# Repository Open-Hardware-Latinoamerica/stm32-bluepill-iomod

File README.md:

# STM32-BluePill Digital I/O Board

This Open Source Hardware PCB proyect is a tool for teach µController (microcontroller) programming. Feel free to use, modifie or improobe it in any way you want. The schematics and the layout was designed on [KiCad EDA Software](https://kicad.org/).

More information (Spanish only): [BluePill STM32 Digital I/O Board v3.0](https://blog.tute-avalos.com/2021/08/18/blue-pill-stm32-digital-i-o-board-v3-0/)

- - -

Este PCB es un poryecto de Hardware Libre y Abierto, pensado para enseñar programación de µControladores (microcontroladores). Sientase libre de usarlo, modificarlo y/o mejorarlo en cualquier sentido que desee. Los esquemáticos y el PCB fueron diseñados utilizando el software [KiCad EDA](https://kicad.org/).

- - -

# Pinout Configuration

## OUTPUTS

| PIN  | Conection     | Active | | PIN  | Conection     | Active |
|------|---------------|--------|-|------|---------------|--------|
| PB9  | LED1 - Red    | LOW    | | PA0  |  Seg E        |  HIGH  |
| PB8  | LED1 - Green  | LOW    | | PA1  |  Seg D        |  HIGH  |
| PB7  | LED1 - Blue   | LOW    | | PA2  |  Seg P        |  HIGH  | 
| PB6  | LED2          | LOW    | | PA3  |  Seg C        |  HIGH  |
| PB5  | LED3          | LOW    | | PA4  |  Seg G        |  HIGH  |
| PB4  | LED4          | LOW    | | PA5  |  Seg B        |  HIGH  |
| PC13 | Build-in LED  | LOW    | | PA6  |  Seg F        |  HIGH  |
|  -   |      -        |   -    | | PA7  |  Seg A        |  HIGH  |
|  -   |      -        |   -    | | PB0  |  Disp 1 (MSD) |  LOW   |
|  -   |      -        |   -    | | PB1  |  Disp 2       |  LOW   |
|  -   |      -        |   -    | | PB10 |  Disp 3       |  LOW   |
|  -   |      -        |   -    | | PB11 |  Disp 4 (LSD) |  LOW   |

## INPUTS

| PIN  | Conection     | Active |
|------|---------------|--------|
| PA15 | Rotary - A    | LOW    |
| PB3  | Rotary - B    | LOW    |
| PA8  | Rotary Switch | LOW    |
| PB15 | Button 1      | LOW    |
| PB14 | Button 2      | LOW    |
| PB13 | Button 3      | LOW    |
| PB12 | Button 4      | LOW    |

## Reference

## Images

|  | |
|-|-|
|<p style="text-align:center;">top layout</p>|<p style="text-align:center;">bottom layout</p>|

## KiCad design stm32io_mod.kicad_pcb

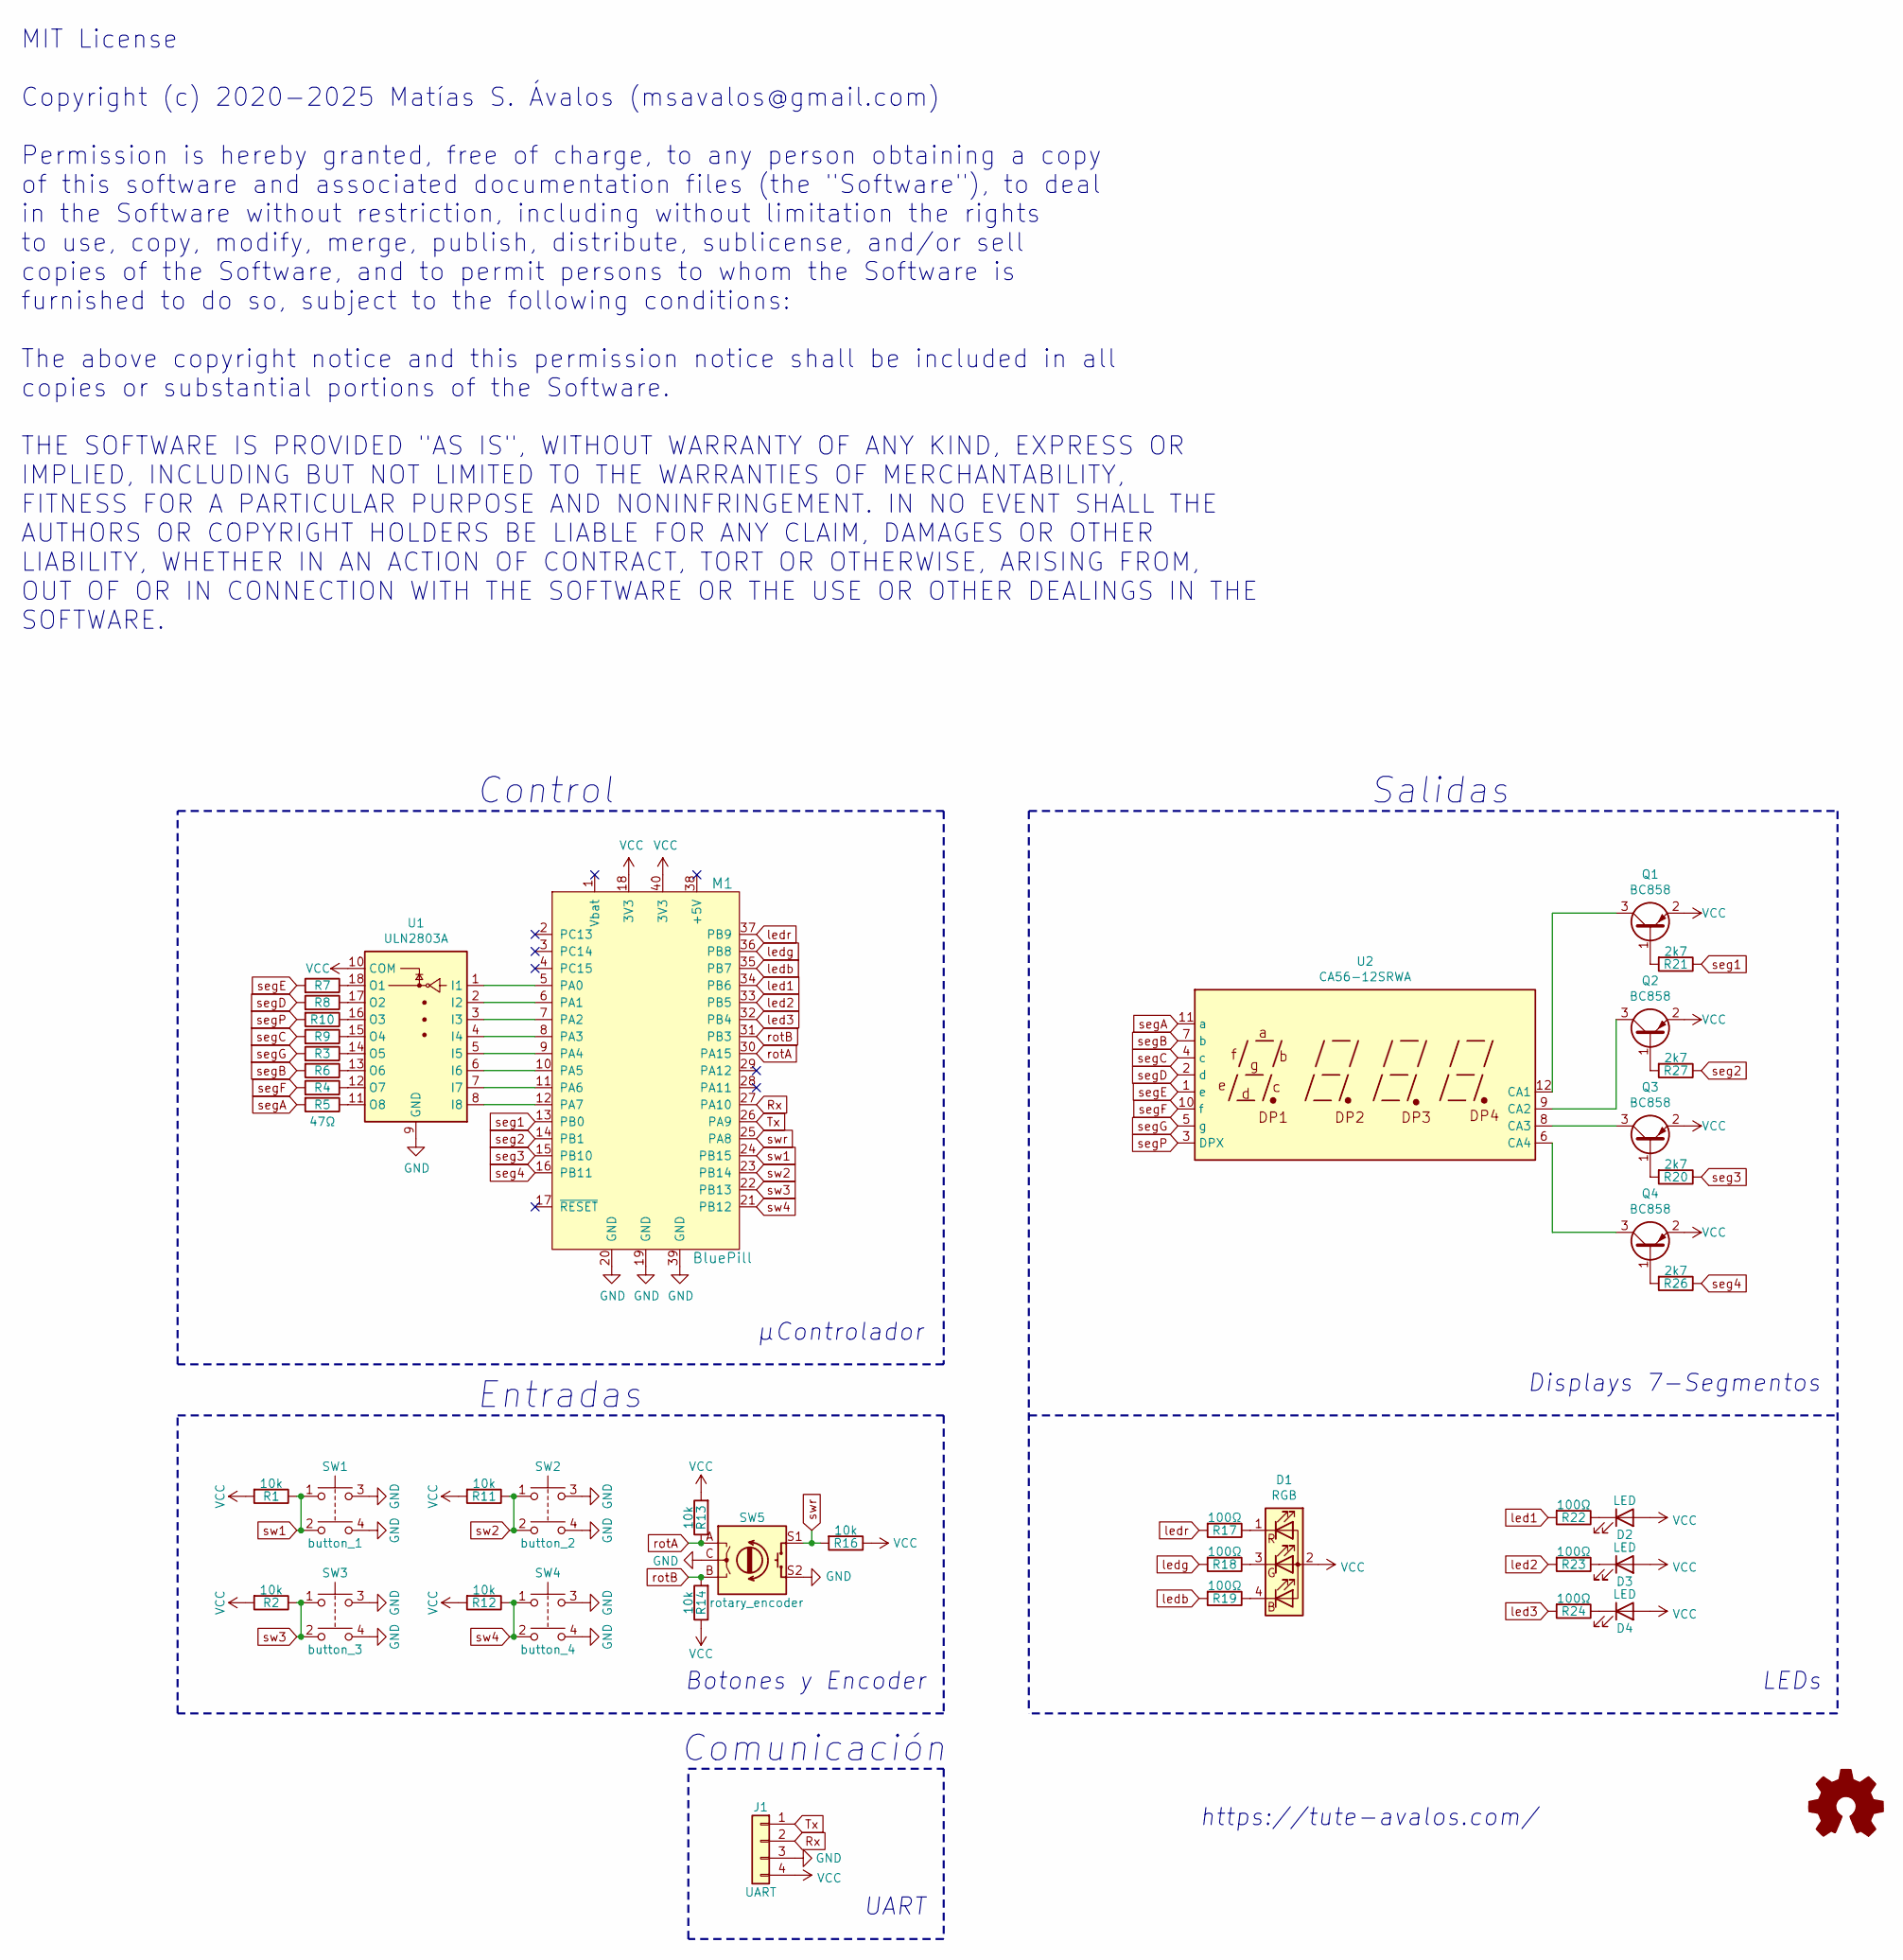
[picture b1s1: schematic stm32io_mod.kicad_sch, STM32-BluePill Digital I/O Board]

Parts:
D1: RGB; LED_D5.0mm-4_RGB
D2, D3, D4: LED; LED_D3.0mm_Clear
J1: UART; PinHeader_1x04_P2.54mm_Vertical
M1: BluePill
Q1, Q2, Q3, Q4: BC858; SOT-23
R1, R2, R11, R12, R13, R14, R16: 10k; R_0805_2012Metric_Pad1.15x1.40mm_HandSolder
R3, R4, R5, R6, R7, R8, R9, R10: 47Ω; R_0805_2012Metric_Pad1.15x1.40mm_HandSolder
R17, R18, R19, R22, R23, R24: 100Ω; R_0805_2012Metric_Pad1.15x1.40mm_HandSolder
R20, R21, R26, R27: 2k7; R_0805_2012Metric_Pad1.15x1.40mm_HandSolder
SW1: button_1; SW_TH_Tactile_Omron_B3F-10xx
SW2: button_2; SW_TH_Tactile_Omron_B3F-10xx
SW3: button_3; SW_TH_Tactile_Omron_B3F-10xx
SW4: button_4; SW_TH_Tactile_Omron_B3F-10xx
SW5: rotary_encoder; RotaryEncoder_Alps_EC11E-Switch_Vertical_H20mm
U1: ULN2803A; SOIC-18W_7.5x11.6mm_P1.27mm
U2: CA56-12SRWA

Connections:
GND: J1.3, M1.19 (GND), M1.20 (GND), M1.39 (GND), SW1.3, SW1.4, SW2.3, SW2.4, SW3.3, SW3.4, SW4.3, SW4.4, SW5.C, SW5.S2, U1.9 (GND)
unnamed: D1.1 (RK), R17.1
unnamed: D1.3 (GK), R18.1
unnamed: D1.4 (BK), R19.1
unnamed: D2.1 (K), R22.1
unnamed: D3.1 (K), R23.1
unnamed: D4.1 (K), R24.1
unnamed: M1.5 (PA0), U1.1 (I1)
unnamed: M1.6 (PA1), U1.2 (I2)
unnamed: M1.7 (PA2), U1.3 (I3)
unnamed: M1.8 (PA3), U1.4 (I4)
unnamed: M1.9 (PA4), U1.5 (I5)
unnamed: M1.10 (PA5), U1.6 (I6)
unnamed: M1.11 (PA6), U1.7 (I7)
unnamed: M1.12 (PA7), U1.8 (I8)
unnamed: Q1.1 (B), R21.2
unnamed: Q1.3 (C), U2.12 (CA1)
unnamed: Q2.1 (B), R27.2
unnamed: Q2.3 (C), U2.9 (CA2)
unnamed: Q3.1 (B), R20.2
unnamed: Q3.3 (C), U2.8 (CA3)
unnamed: Q4.1 (B), R26.2
unnamed: Q4.3 (C), U2.6 (CA4)
unnamed: R3.1, U1.14 (O5)
unnamed: R4.1, U1.12 (O7)
unnamed: R5.1, U1.11 (O8)
unnamed: R6.1, U1.13 (O6)
unnamed: R7.1, U1.18 (O1)
unnamed: R8.1, U1.17 (O2)
unnamed: R9.1, U1.15 (O4)
unnamed: R10.1, U1.16 (O3)
Rx: J1.2, M1.27 (PA10)
Tx: J1.1, M1.26 (PA9)
VCC: D1.2 (A), D2.2 (A), D3.2 (A), D4.2 (A), J1.4, M1.18 (3V3), M1.40 (3V3), Q1.2 (E), Q2.2 (E), Q3.2 (E), Q4.2 (E), R1.2, R2.2, R11.2, R12.2, R13.2, R14.1, R16.1, U1.10 (COM)
led1: M1.34 (PB6), R22.2
led2: M1.33 (PB5), R23.2
led3: M1.32 (PB4), R24.2
ledb: M1.35 (PB7), R19.2
ledg: M1.36 (PB8), R18.2
ledr: M1.37 (PB9), R17.2
rotA: M1.30 (PA15), R13.1, SW5.A
rotB: M1.31 (PB3), R14.2, SW5.B
seg1: M1.13 (PB0), R21.1
seg2: M1.14 (PB1), R27.1
seg3: M1.15 (PB10), R20.1
seg4: M1.16 (PB11), R26.1
segA: R5.2, U2.11 (a)
segB: R6.2, U2.7 (b)
segC: R9.2, U2.4 (c)
segD: R8.2, U2.2 (d)
segE: R7.2, U2.1 (e)
segF: R4.2, U2.10 (f)
segG: R3.2, U2.5 (g)
segP: R10.2, U2.3 (DPX)
sw1: M1.24 (PB15), R1.1, SW1.1, SW1.2
sw2: M1.23 (PB14), R11.1, SW2.1, SW2.2
sw3: M1.22 (PB13), R2.1, SW3.1, SW3.2
sw4: M1.21 (PB12), R12.1, SW4.1, SW4.2
swr: M1.25 (PA8), R16.2, SW5.S1

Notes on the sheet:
Displays 7-Segmentos
Salidas
Entradas
Comunicación
Botones y Encoder
LEDs
Control
UART
µControlador
MIT License Copyright (c) 2020-2025 Matías S. Ávalos (msavalos@gmail.com) Permission is hereby granted, free of charge, to any person obtaining a copy of this software and associated documentation files (the "Software"), to deal in the Software without restriction, including without limitation the 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
https://tute-avalos.com/

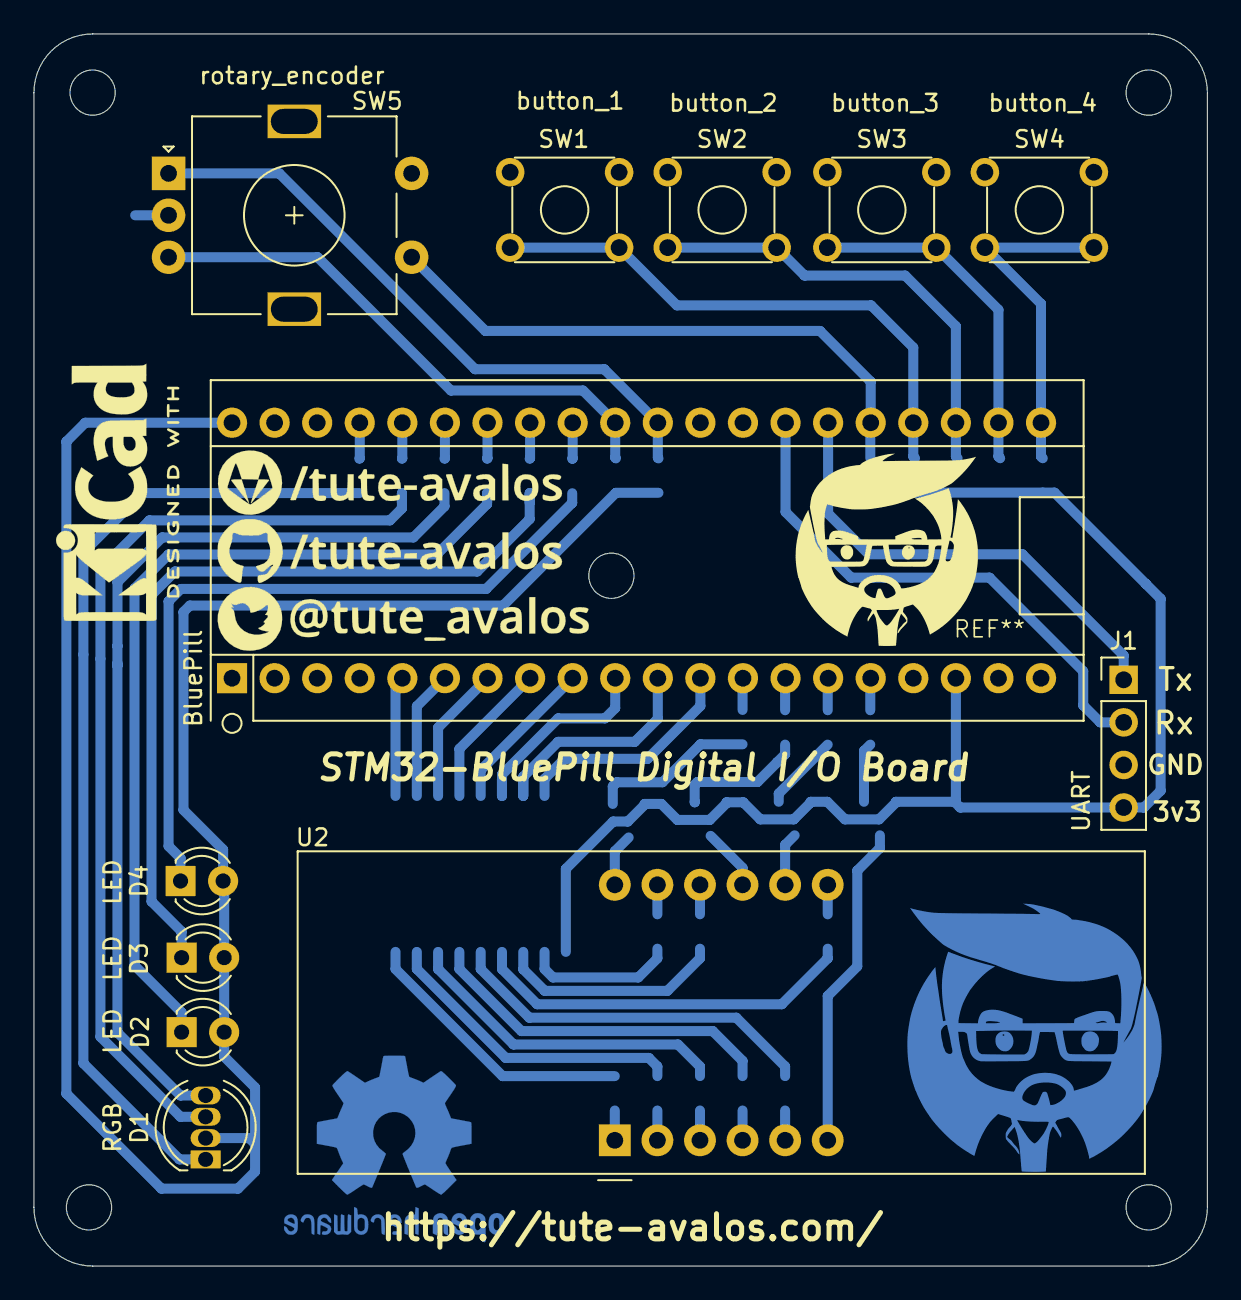
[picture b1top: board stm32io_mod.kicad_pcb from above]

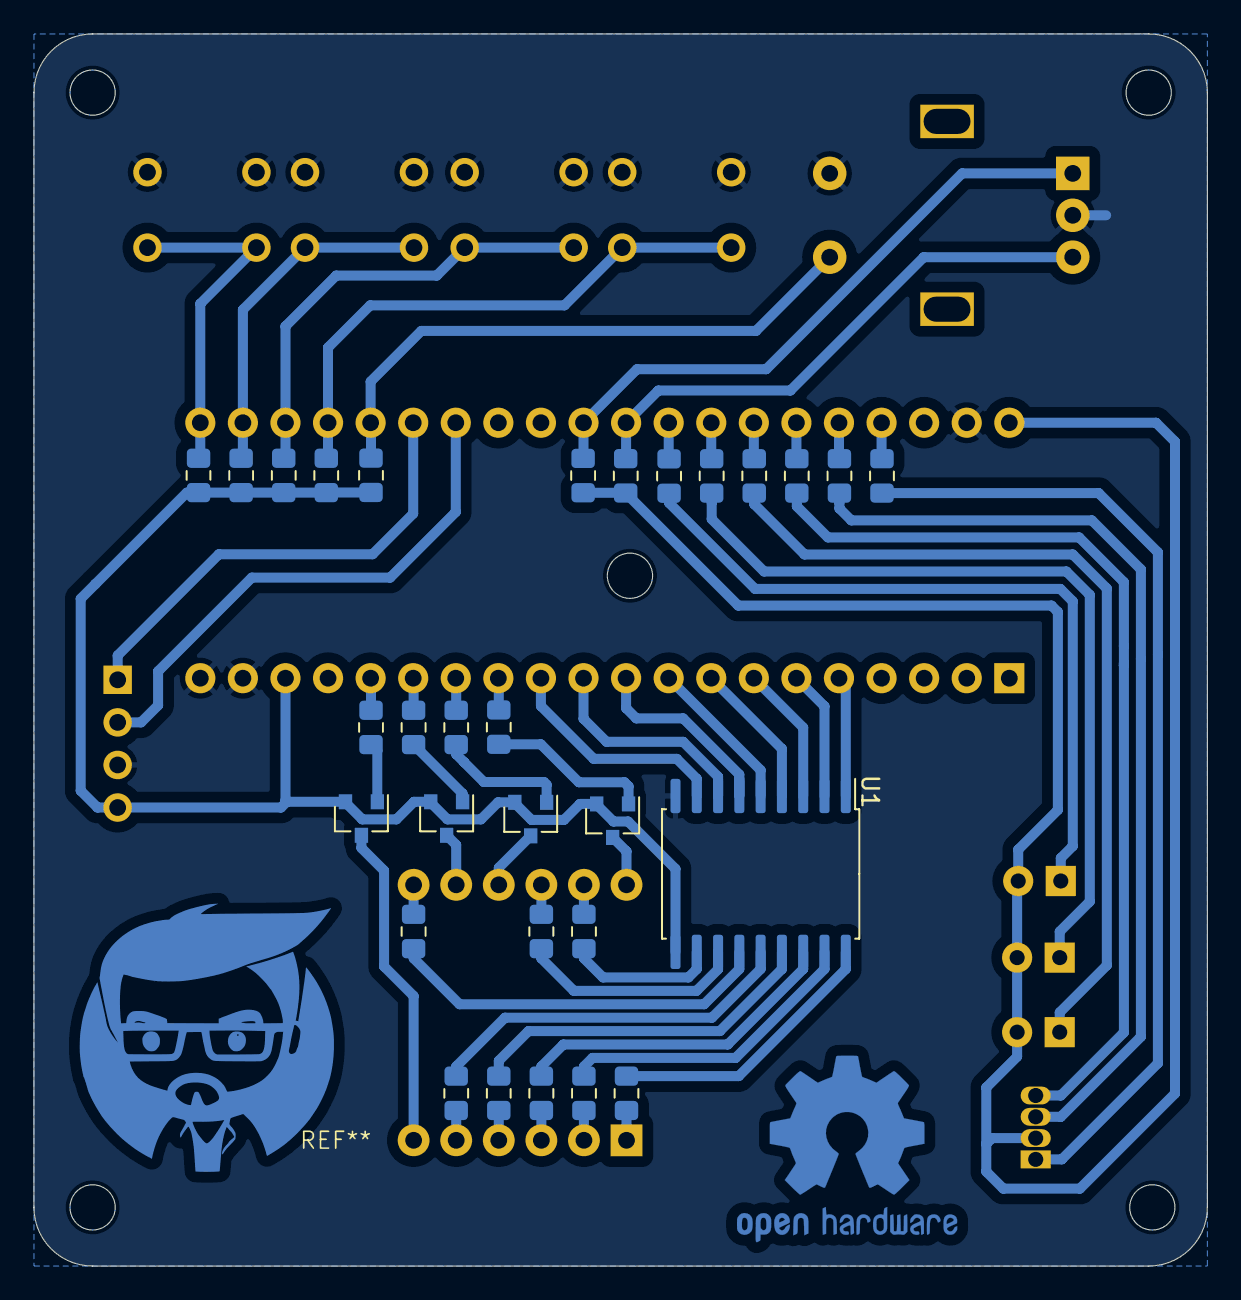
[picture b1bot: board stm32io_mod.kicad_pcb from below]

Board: 2 copper layers, 70.0 x 73.5 mm, 43 parts (30 on the bottom side), 59 nets.

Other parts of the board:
Social: Links; electronlinux-social-22x12

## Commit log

2020-02-27 Primer commit
2020-02-28 Se añade licencia
2020-02-29 Cambio de README a README.md
2020-02-29 Descripción de pines en el README
2020-03-02 cambio de resistencias a smd
2020-03-02 Pequeño arreglo del README
2020-03-03 Pequeños arreglos en el PCB
2020-03-10 Agregado VCC al pinhead de la UART
2020-03-11 Se agregó una linea de gnd entre el rotary
2020-05-21 Cambio de polaridad de los LEDs 2-5
2020-06-12 Se corrigió la polaridad de los leds y el README
2020-06-12 Se incluyen las imagenes/renders y link al blog
2020-06-23 Corrección en la serigrafía de la bluepill y UART
2020-09-03 Cambio de lugar del rotary
2020-09-06 retoques finales
2021-01-03 Se modificaron las imágenes de referencias y tablas
2021-01-11 Agregadas imagenes en el README
2021-08-18 Se mejoró el plano de masa
2021-08-18 Corrección del link al post
2021-08-18 Corrección en el README.md
2021-11-08 Update README.md
    https://forum.kicad.info/t/warning-avoid-all-links-to-kicad-pcb-org-use-kicad-org/31521
2025-02-27 se actualizan las serigrafías a nuevos logos y nueva url
2025-02-27 Se modifica el readme
2025-03-21 Se ajustaron los screenshots
2025-03-21 ajuste menor en el README

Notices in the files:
stm32io_mod.kicad_pcb:
MIT License (https://opensource.org/licenses/MIT)
